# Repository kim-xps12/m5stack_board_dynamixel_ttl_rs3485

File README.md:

# DYNAMIXEL TTL interface board for M5Stack

## About
M5StackからDYNAMIXEL TTL対応のシリアルサーボを操作するためのオリジナル基板です．KiCAD 7で設計しました．

## Appearance

## Usage

配線と動作の様子はこちら．

https://www.youtube.com/watch?v=RdcbOagrEI8

## Schematics

## Pin assign

## Layout

unit: millimetre

## BOM
| Symbol | Model Number |URL, Values|
| --- | --- | --- |
| Q1  | 2SA1162GR<br> | [https://akizukidenshi.com/catalog/g/gI-02702/](https://akizukidenshi.com/catalog/g/gI-02702/)<br> |
| U1  | MAX3485ED<br> | [https://akizukidenshi.com/catalog/g/gI-16211/](https://akizukidenshi.com/catalog/g/gI-16211/)<br> |
| U2  | AP7333<br> | [https://akizukidenshi.com/catalog/g/gI-11360/](https://akizukidenshi.com/catalog/g/gI-11360/)<br> |
| J1  | JST B4B-PH-K-S(LF)(SN) | [https://www.sengoku.co.jp/mod/sgk\_cart/detail.php?code=4DK2-SDDB](https://www.sengoku.co.jp/mod/sgk_cart/detail.php?code=4DK2-SDDB)<br> |
| J2  | HY2.0-4PZZ | [https://ssci.to/1122](https://ssci.to/1122)<br> |
| J3  | B3B-EH(LF)(SN) | [https://www.sengoku.co.jp/mod/sgk_cart/detail.php?code=EEHD-4KBP](https://www.sengoku.co.jp/mod/sgk_cart/detail.php?code=EEHD-4KBP)<br> |
| R   | 0608 inch / 1608 jis metric | R1=7.5k, R2=20k, R3=R4=2.2k |
| C   | 0608 inch / 1608 jis metric | C1=0.1 u, C2=C3=1u |

## Exammple code

### Arduino IDE

1. Dynamixel2Arduinoライブラリをインストールします．ROBOTIS e-manualを参照してください．
    Install Dynamixel2Arduino library from ROBOTIS e-manual.
   
    ROBOTIS e-manual : [日本語](https://emanual.robotis.com/docs/en/software/arduino_ide_jp/), [English](https://emanual.robotis.com/docs/en/software/arduino_ide/)

3. Arduino IDEで[同封のサンプルコード](example_m5core2_dynamixel_arduino_ide/example_m5core2_dynamixel_arduino_ide.ino)を開いて，M5Stack Core2へ書き込みます．
    Open the enclosed [example code](example_m5core2_dynamixel_arduino_ide/example_m5core2_dynamixel_arduino_ide.ino) with Arduino IDE and write it to M5Stack Core2.

4. [Usage](#usage) の動画を参考に配線して電源を投入してください．
    Please refer to the Usage video to wire and turn on the power.

### PlatformIO

comming soon :)

## NOTE
ご自身の環境で本リポジトリを利用する際は，`HY2.0-4P.kicad_mod` を適切なライブラリへインポートしてお使いください．
作者はグローバルライブラリへインポートして複数プロジェクトから利用できるようにしています．

When using this repository in your own environment, please import HY2.0-4P.kicad_mod into the appropriate library. 
I import it into the global library so that it can be used from other projects as well.

## Distribution
本基板（完成品）はboothで頒布中です．よろしければご利用ください．

[https://b-sky-lab.booth.pm/items/5576375](https://b-sky-lab.booth.pm/items/5576375)

## Disclaimer
MITライセンスでの公開です．本設計および頒布した基板において生じた一切の損害等について作者は責任を負いません．予めご了承ください．

This is released under the MIT license. The author is not responsible for any damage caused to this design or the distributed board. Please note.

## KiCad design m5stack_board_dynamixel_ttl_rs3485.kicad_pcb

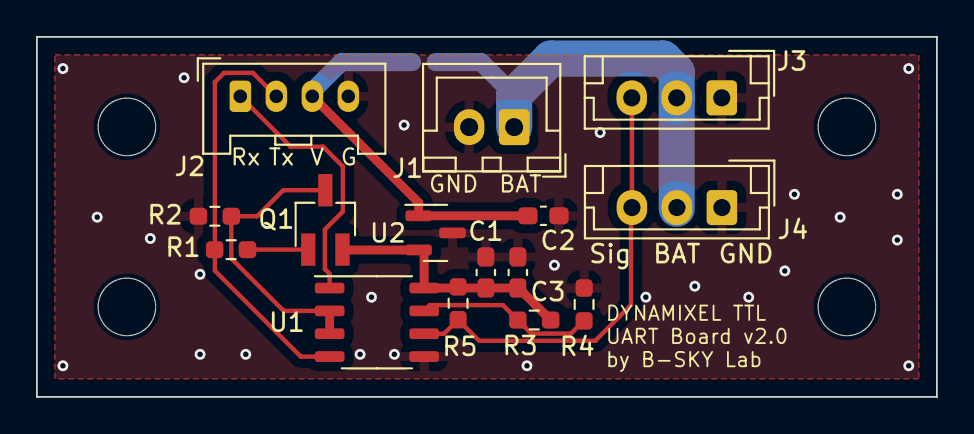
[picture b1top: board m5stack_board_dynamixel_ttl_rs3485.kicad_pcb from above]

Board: 2 copper layers, 50.0 x 20.0 mm, 20 parts (1 on the bottom side), 10 nets.

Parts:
C1: 0.1u; C_0603_1608Metric_Pad1.08x0.95mm_HandSolder
C2, C3: 1u; C_0603_1608Metric_Pad1.08x0.95mm_HandSolder
J1: B2B-XH-A(LF)(SN); JST_XH_B2B-XH-A_1x02_P2.50mm_Vertical
J2: WAFER-HY2.0-4PZZ; HY2.0-4P
J3, J4: B3B-EH-A(LF)(SN); JST_EH_B3B-EH-A_1x03_P2.50mm_Vertical
JP1: Jumper_2_Open; SolderJumper-2_P1.3mm_Open_RoundedPad1.0x1.5mm
MH1, MH2, MH3, MH4: MountingHole_3.2mm_M3
Q1: 2SA1162GR; SC-59_Handsoldering
R1: 7.5k; R_0603_1608Metric_Pad0.98x0.95mm_HandSolder
R2: 20k; R_0603_1608Metric_Pad0.98x0.95mm_HandSolder
R3, R4: 2.2k; R_0603_1608Metric_Pad0.98x0.95mm_HandSolder
R5: 10k; R_0603_1608Metric_Pad0.98x0.95mm_HandSolder
U1: MAX3485; SOP-8_3.9x4.9mm_P1.27mm
U2: AP7333-33SAG; SOT-23

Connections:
+3.3V: C1.1, C3.1, Q1.2 (E), R3.2, R5.2, U1.8 (VCC), U2.2 (VO)
+5V: C2.1, J2.3, JP1.2 (B), U2.1 (VI)
/BAT: J1.1, J3.2, J4.2, JP1.1 (A)
/STS_RX: J2.1, U1.1 (RO)
/STS_TX: J2.2, R1.1, U1.4 (DI)
/signal: J3.3, J4.3, R5.1, U1.6 (A)
GND: C1.2, C2.2, C3.2, J1.2, J2.4, J3.1, J4.1, R2.1, R4.1, U1.5 (GND), U2.3 (GND)
unnamed: Q1.1 (B), R1.2
unnamed: Q1.3 (C), R2.2, U1.2 (~RE), U1.3 (DE)
unnamed: R3.1, R4.2, U1.7 (B)

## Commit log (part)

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2024-03-16 rename example code
2024-04-16 fix example-code link in README.md
2024-05-12 update README (add pin assign and layout)
2024-05-20 print servo status (rpm) on M5 display
2024-09-20 update board
2024-09-20 update example, fix pin assign for based on PORT.C UART
